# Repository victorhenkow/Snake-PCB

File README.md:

# Snake-PCB
A Snake game made using an Atmega328p and an LED matrix implemented on a PCB. The circuit design, the PCB layout and the code to run the game are all uploaded.

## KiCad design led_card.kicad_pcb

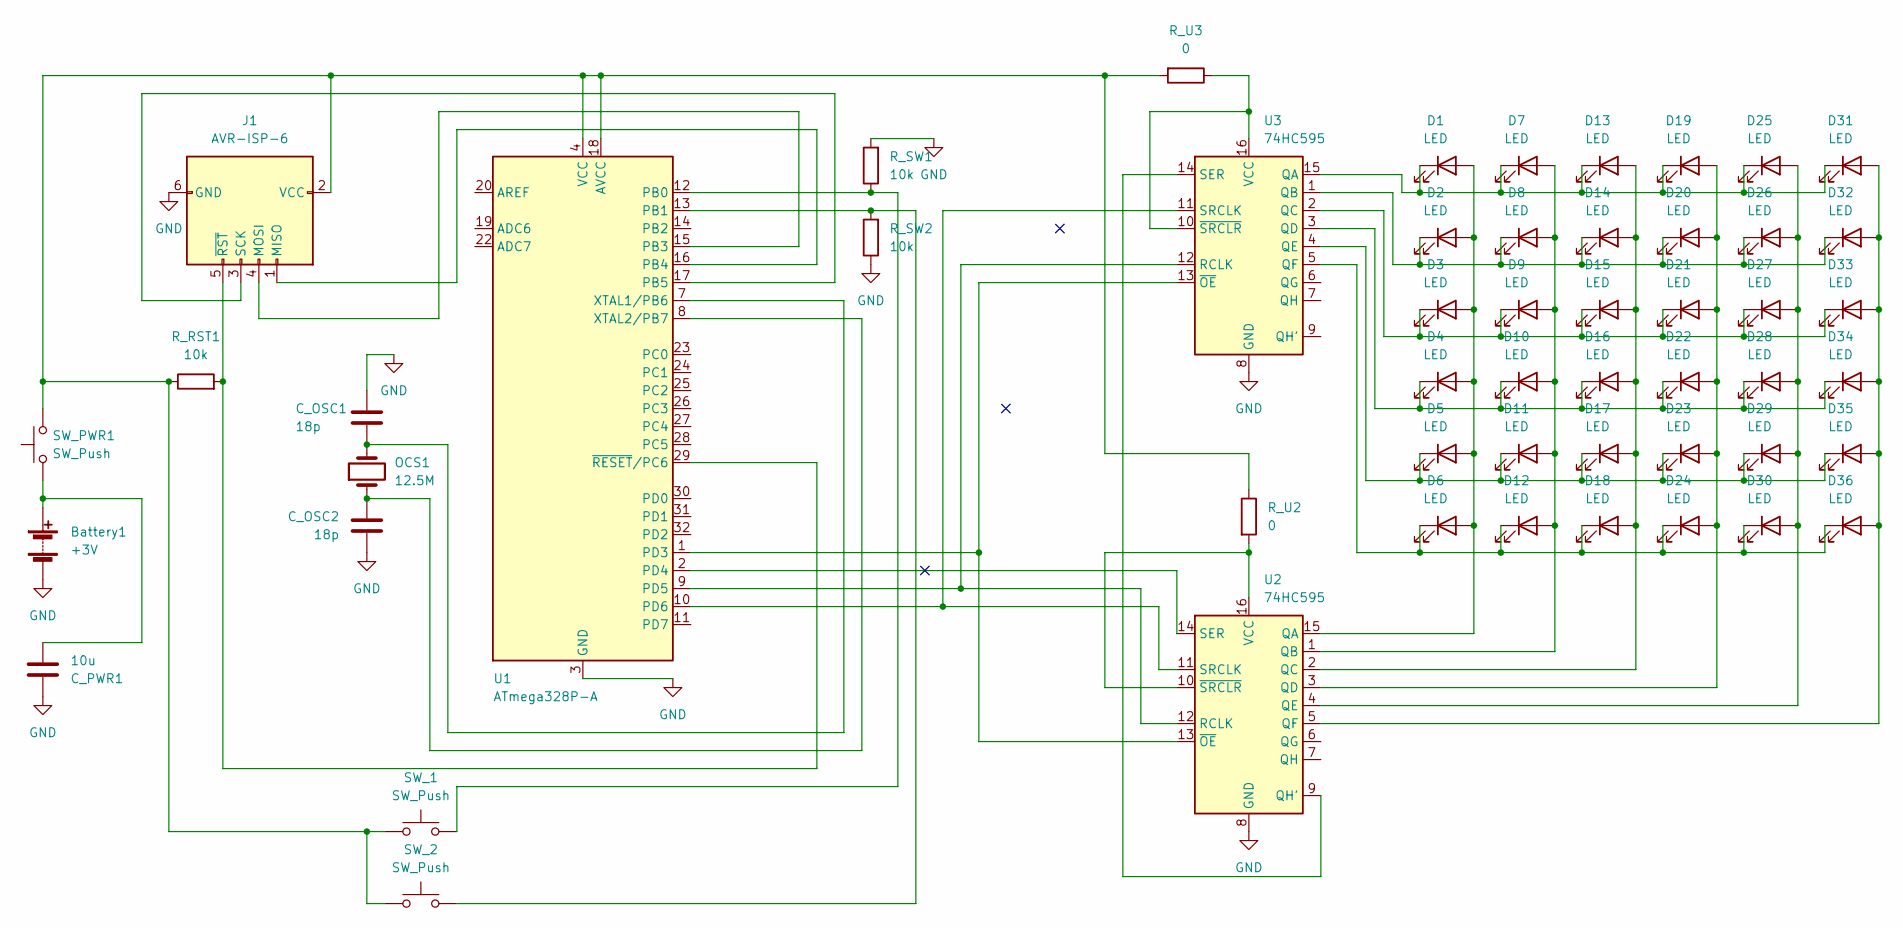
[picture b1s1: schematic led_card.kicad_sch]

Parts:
Battery1: +3V; BatteryHolder_LINX_BAT-HLD-012-SMT
C_OSC1, C_OSC2: 18p; C_1206_3216Metric
C_PWR1: 10u; C_1206_3216Metric
D1, D2, D3, D4, D5, D6, D7, D8, D9, D10, D11, D12, D13, D14, D15, D16, D17, D18, D19, D20, D21, D22, D23, D24, D25, D26, D27, D28, D29, D30, D31, D32, D33, D34, D35, D36: LED; LED_1206_3216Metric
J1: AVR-ISP-6; IDC-Header_2x03_P2.54mm_Horizontal
OCS1: 12.5M; Crystal_SMD_HC49-SD
R_RST1: 10k; R_1206_3216Metric
R_SW1, R_SW2: 10k; R_1206_3216Metric
R_U2, R_U3: 0; R_1206_3216Metric
SW_1, SW_2: SW_Push; SW_Push_1P1T_NO_6x6mm_H9.5mm
SW_PWR1: SW_Push; SW_Push_1P1T_NO_6x6mm_H9.5mm
U1: ATmega328P-A; TQFP-32_7x7mm_P0.8mm
U2, U3: 74HC595; SOIC-16W_7.5x10.3mm_P1.27mm

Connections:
GND: Battery1.2 (-), C_OSC1.1, C_OSC2.2, C_PWR1.1, J1.6 (GND), R_SW1.2, R_SW2.1, U1.3 (GND), U1.5 (GND), U1.21 (GND), U2.8 (GND), U3.8 (GND)
unnamed: Battery1.1 (+), C_PWR1.2, SW_PWR1.1
unnamed: C_OSC1.2, OCS1.2, U1.7 (XTAL1/PB6)
unnamed: C_OSC2.1, OCS1.1, U1.8 (XTAL2/PB7)
unnamed: D1.1 (K), D7.1 (K), D13.1 (K), D19.1 (K), D25.1 (K), D31.1 (K), U3.15 (QA)
unnamed: D1.2 (A), D2.2 (A), D3.2 (A), D4.2 (A), D5.2 (A), D6.2 (A), U2.15 (QA)
unnamed: D4.1 (K), D10.1 (K), D16.1 (K), D22.1 (K), D28.1 (K), D34.1 (K), U3.3 (QD)
unnamed: D7.2 (A), D8.2 (A), D9.2 (A), D10.2 (A), D11.2 (A), D12.2 (A), U2.1 (QB)
unnamed: D5.1 (K), D11.1 (K), D17.1 (K), D23.1 (K), D29.1 (K), D35.1 (K), U3.4 (QE)
unnamed: D6.1 (K), D12.1 (K), D18.1 (K), D24.1 (K), D30.1 (K), D36.1 (K), U3.5 (QF)
unnamed: D13.2 (A), D14.2 (A), D15.2 (A), D16.2 (A), D17.2 (A), D18.2 (A), U2.2 (QC)
unnamed: D2.1 (K), D8.1 (K), D14.1 (K), D20.1 (K), D26.1 (K), D32.1 (K), U3.1 (QB)
unnamed: D3.1 (K), D9.1 (K), D15.1 (K), D21.1 (K), D27.1 (K), D33.1 (K), U3.2 (QC)
unnamed: D19.2 (A), D20.2 (A), D21.2 (A), D22.2 (A), D23.2 (A), D24.2 (A), U2.3 (QD)
unnamed: D25.2 (A), D26.2 (A), D27.2 (A), D28.2 (A), D29.2 (A), D30.2 (A), U2.4 (QE)
unnamed: D31.2 (A), D32.2 (A), D33.2 (A), D34.2 (A), D35.2 (A), D36.2 (A), U2.5 (QF)
unnamed: J1.1 (MISO), U1.16 (PB4)
unnamed: J1.2 (VCC), R_RST1.1, R_U2.1, R_U3.2, SW_1.1, SW_2.1, SW_PWR1.2, U1.4 (VCC), U1.6 (VCC), U1.18 (AVCC)
unnamed: J1.3 (SCK), U1.17 (PB5)
unnamed: J1.4 (MOSI), U1.15 (PB3)
unnamed: J1.5 (~RST), R_RST1.2, U1.29 (~RESET/PC6)
unnamed: R_SW1.1, SW_1.2, U1.12 (PB0)
unnamed: R_SW2.2, SW_2.2, U1.13 (PB1)
unnamed: R_U2.2, U2.10 (~SRCLR), U2.16 (VCC)
unnamed: R_U3.1, U3.10 (~SRCLR), U3.16 (VCC)
unnamed: U1.1 (PD3), U2.13 (~OE), U3.13 (~OE)
unnamed: U1.2 (PD4), U2.14 (SER)
unnamed: U1.9 (PD5), U2.12 (RCLK), U3.12 (RCLK)
unnamed: U1.10 (PD6), U2.11 (SRCLK), U3.11 (SRCLK)
unnamed: U2.9 (QH'), U3.14 (SER)

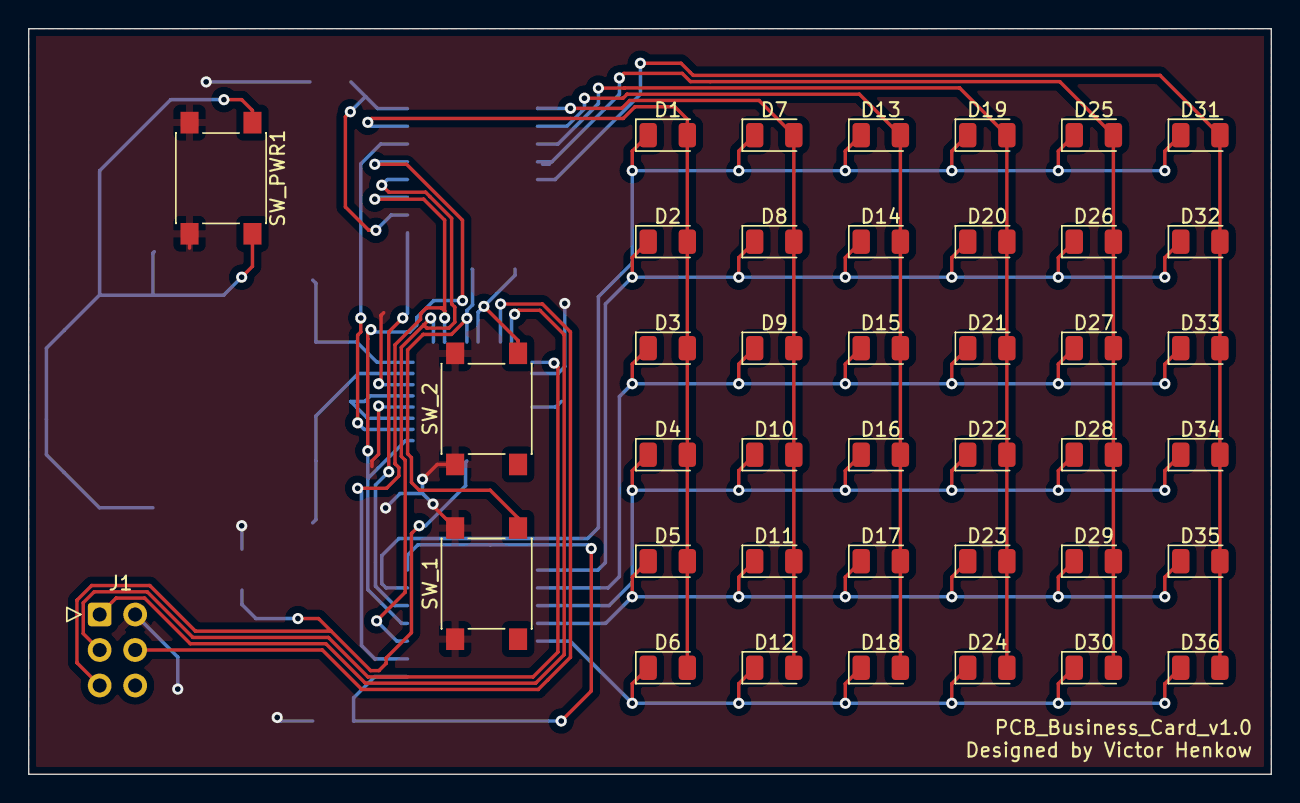
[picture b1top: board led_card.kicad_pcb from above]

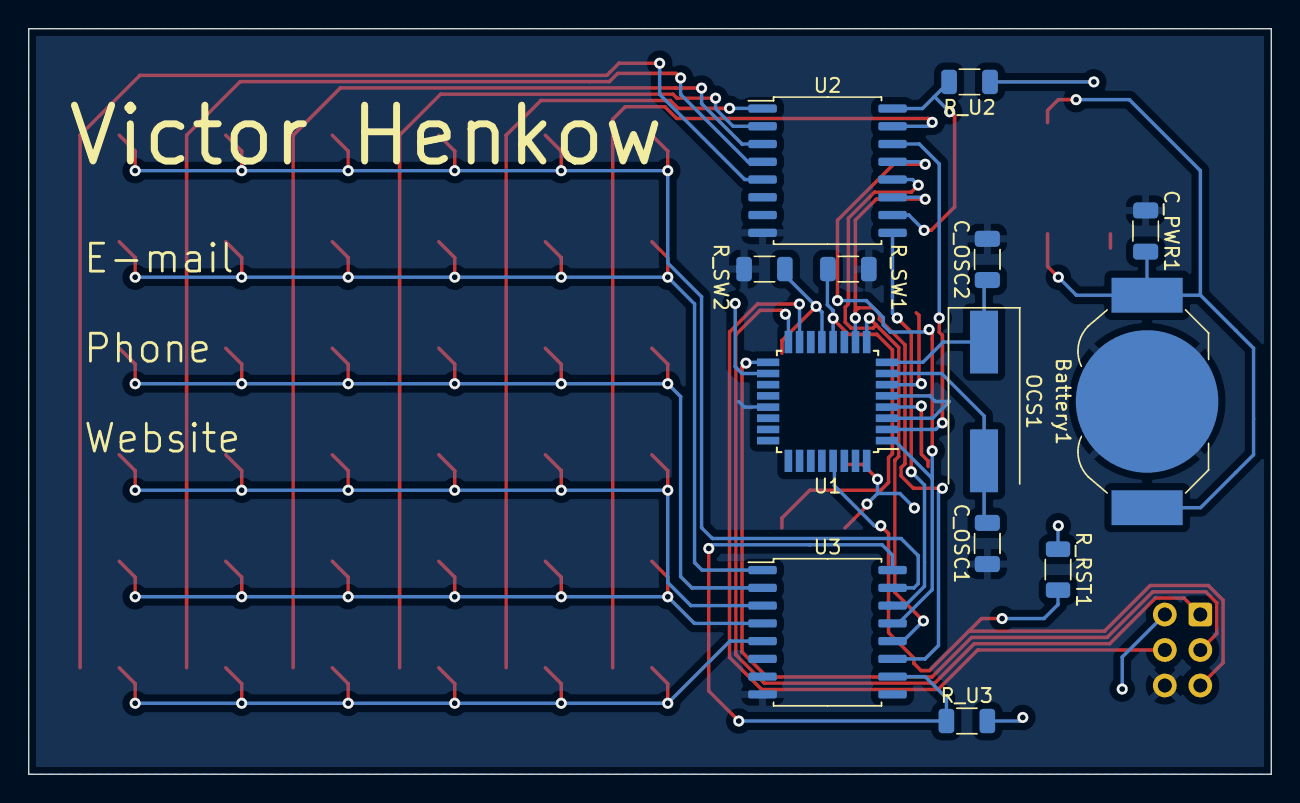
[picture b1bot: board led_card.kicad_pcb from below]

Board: 2 copper layers, 88.9 x 53.3 mm, 53 parts (13 on the bottom side), 30 nets.

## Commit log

2025-04-22 Add files via upload
    A first commit
